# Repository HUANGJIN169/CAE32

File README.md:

# CAE32

CAE32 es un proyecto de construcción y desarrollo de todas las etapas de un volante para videojuegos de PC,
para el sistema operativo de GNU/Linux.

## Las etapas son:

* Diseño PCB
* Firmware
* Driver (Kernel module)
* Configuración y calibración por medio de una interfaz de usuario (GTK-3)
* Diseño de mecanismos para pedales, palanca de cambios y volante
* Diseño PCB de potencia para el control del motor de retroalimentación (FFB)

## Descripción detallada

### Microcontroladores

Para esta primera versión de Harware, se crean 3 PCB

1. Placa principal (ESP32-S3)

2. Placa para la captura de señales analogicas (STM32G070KBT6)

3. Placa con el sensor hall (MT9105ET)

### Firmware

Estoy usando el framework de Espressif (ESP-IDF)

Se usa el microcontrolador STM32G070KBT6, en conjunto con el software
STM32CubeIDE y para programarlo es necesario la utilidad STM32CubeProgrammer,
ademas de una conexión con un "USB-UART bridge"

### Interfaz de usuario

La interfaz está desarrollada con el framework (GTK 3), esta permitirá hacer configuraciones, como por ejemplo:

* Visualización de los datos gráficamente y textual (consola)
* Tipo de transmisión (Manual, Automática, Secuencial, custom) **De forma nativa**
* Límites de los pedales, sensibilidad 
* Tipo de pedal
	* Entrada analógica (Potenciómetro, efecto hall)
	* Entrada SPI,I2c (Célula de carga)
* Actualización de firmware

Diseño de interfaz hasta el momento.

**Para compilar el proyecto puedes usar el contenedor o construirlo en tu sistema(cumpliendo con las dependencias),
revisa la wiki para mas información**

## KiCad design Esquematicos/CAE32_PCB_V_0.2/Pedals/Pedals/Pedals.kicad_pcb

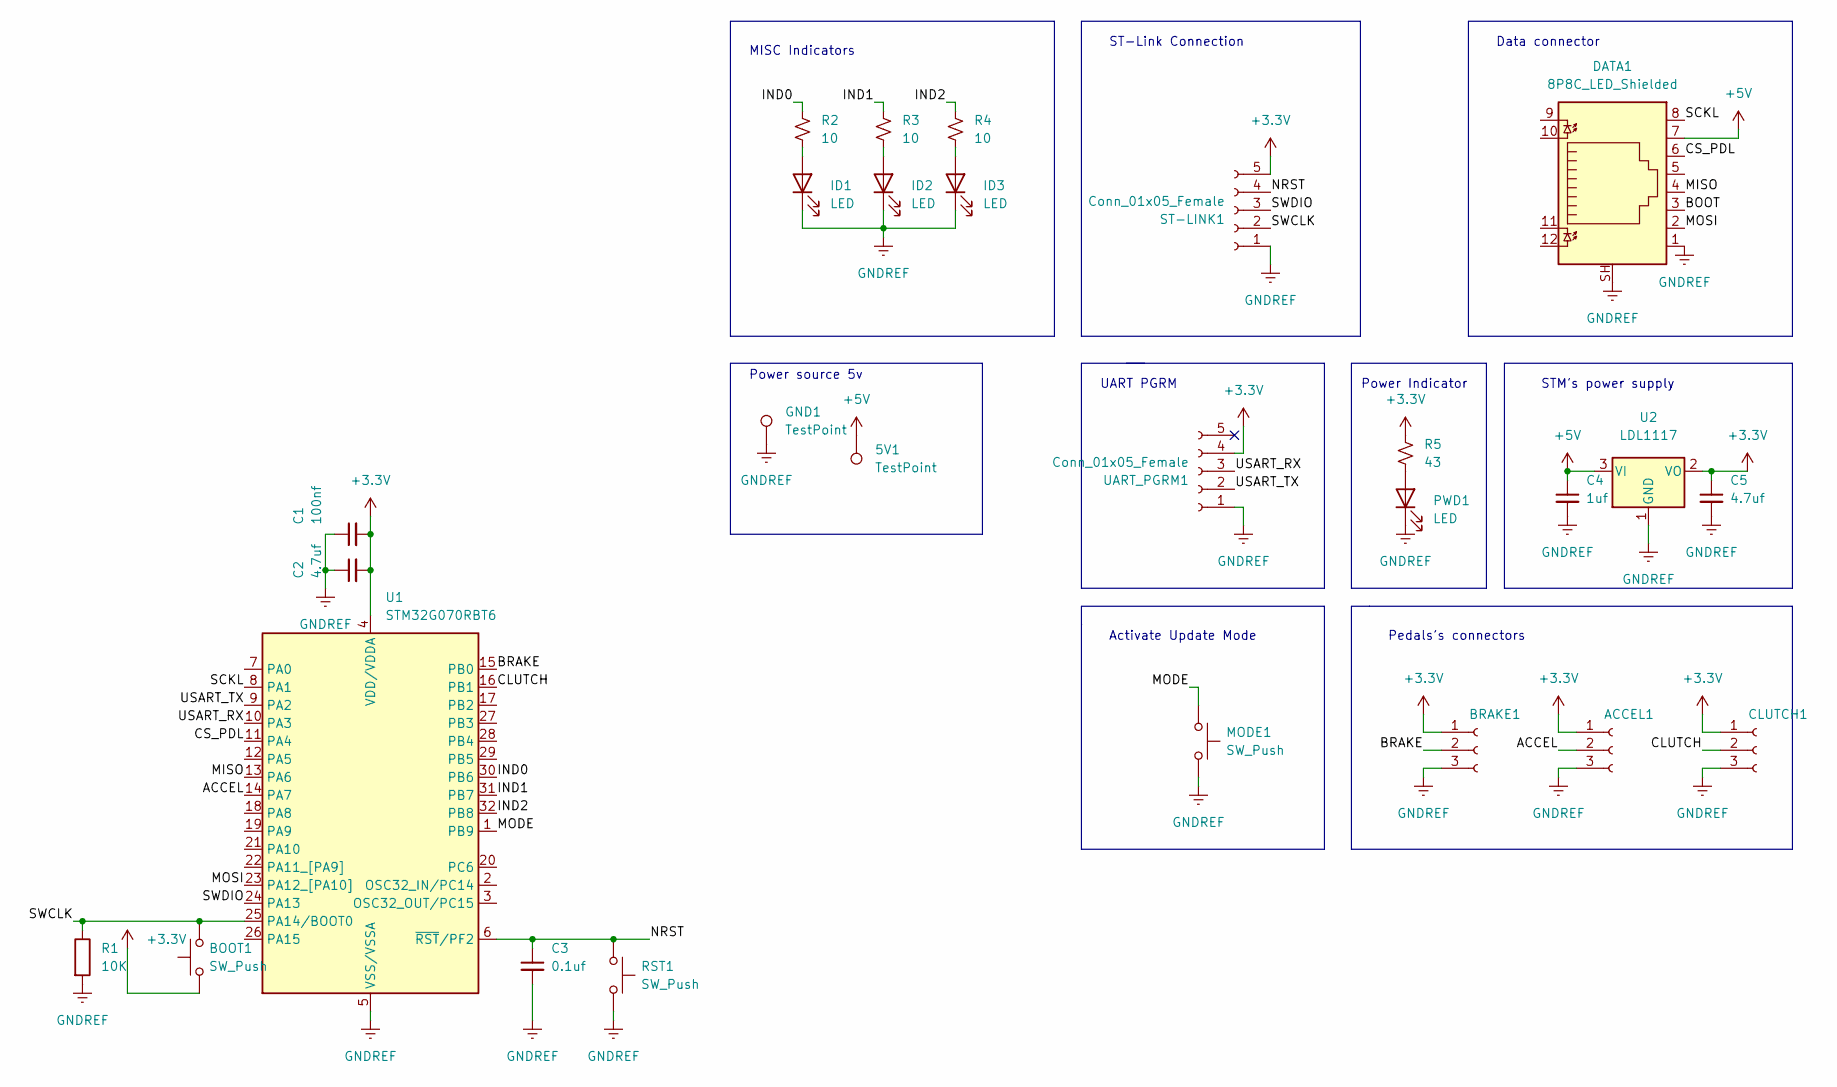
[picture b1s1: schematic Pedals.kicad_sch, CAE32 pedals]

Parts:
5V1: TestPoint; TestPoint_Pad_D3.0mm
ACCEL1: Conn_01x03_Female; JST_EH_B3B-EH-A_1x03_P2.50mm_Vertical
BOOT1: SW_Push; Panasonic_EVQPUM_EVQPUD
BRAKE1: Conn_01x03_Female; JST_EH_B3B-EH-A_1x03_P2.50mm_Vertical
C1: 100nf; C_0805_2012Metric_Pad1.18x1.45mm_HandSolder
C2, C5: 4.7uf; C_0805_2012Metric_Pad1.18x1.45mm_HandSolder
C3: 0.1uf; C_0805_2012Metric_Pad1.18x1.45mm_HandSolder
C4: 1uf; C_0805_2012Metric_Pad1.18x1.45mm_HandSolder
CLUTCH1: Conn_01x03_Female; JST_EH_B3B-EH-A_1x03_P2.50mm_Vertical
DATA1: 8P8C_LED_Shielded; RJ45_Amphenol_RJHSE538X
GND1: TestPoint; TestPoint_Pad_D3.0mm
ID1, ID2, ID3: LED; LED_0805_2012Metric_Pad1.15x1.40mm_HandSolder
MODE1: SW_Push; SW_Push_1P1T_NO_6x6mm_H9.5mm
PWD1: LED; LED_0805_2012Metric_Pad1.15x1.40mm_HandSolder
R1: 10K; R_0805_2012Metric_Pad1.20x1.40mm_HandSolder
R2, R3, R4: 10; R_0805_2012Metric_Pad1.20x1.40mm_HandSolder
R5: 43; R_0805_2012Metric_Pad1.20x1.40mm_HandSolder
RST1: SW_Push; Panasonic_EVQPUM_EVQPUD
ST-LINK1: Conn_01x05_Female; PinHeader_1x05_P2.54mm_Vertical
U1: STM32G070RBT6; LQFP-32_7x7mm_P0.8mm
U2: LDL1117; SOT-223-3_TabPin2
UART_PGRM1: Conn_01x05_Female; PinHeader_1x05_P2.54mm_Vertical

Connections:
+3.3V: ACCEL1.1, BOOT1.1, BRAKE1.1, C1.2, C2.2, C5.1, CLUTCH1.1, R5.1, ST-LINK1.5, U1.4 (VDD/VDDA), U2.2 (VO), UART_PGRM1.4
+5V: 5V1.1, C4.1, DATA1.7, U2.3 (VI)
/ACCEL: ACCEL1.2, U1.14 (PA7)
/BOOT: DATA1.3
/BRAKE: BRAKE1.2, U1.15 (PB0)
/CLUTCH: CLUTCH1.2, U1.16 (PB1)
/CS_PDL: DATA1.6, U1.11 (PA4)
/IND0: R2.1, U1.30 (PB6)
/IND1: R3.1, U1.31 (PB7)
/IND2: R4.1, U1.32 (PB8)
/MISO: DATA1.4, U1.13 (PA6)
/MODE: MODE1.1, U1.1 (PB9)
/MOSI: DATA1.2, U1.23 (PA12_[PA10])
/NRST: C3.1, RST1.1, ST-LINK1.4, U1.6 (~RST/PF2)
/SCKL: DATA1.8, U1.8 (PA1)
/SWCLK: BOOT1.2, R1.1, ST-LINK1.2, U1.25 (PA14/BOOT0)
/SWDIO: ST-LINK1.3, U1.24 (PA13)
/USART_RX: U1.10 (PA3), UART_PGRM1.3
/USART_TX: U1.9 (PA2), UART_PGRM1.2
GNDREF: ACCEL1.3, BRAKE1.3, C1.1, C2.1, C3.2, C4.2, C5.2, CLUTCH1.3, DATA1.1, DATA1.SH, GND1.1, ID1.1 (K), ID2.1 (K), ID3.1 (K), MODE1.2, PWD1.1 (K), R1.2, RST1.2, ST-LINK1.1, U1.5 (VSS/VSSA), U2.1 (GND), UART_PGRM1.1
unnamed: ID1.2 (A), R2.2
unnamed: ID2.2 (A), R3.2
unnamed: ID3.2 (A), R4.2
unnamed: PWD1.2 (A), R5.2

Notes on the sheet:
ST-Link Connection
STM's power supply
Pedals's connectors
Activate Update Mode
Power source 5v
MISC Indicators
Power Indicator
UART PGRM
Data connector

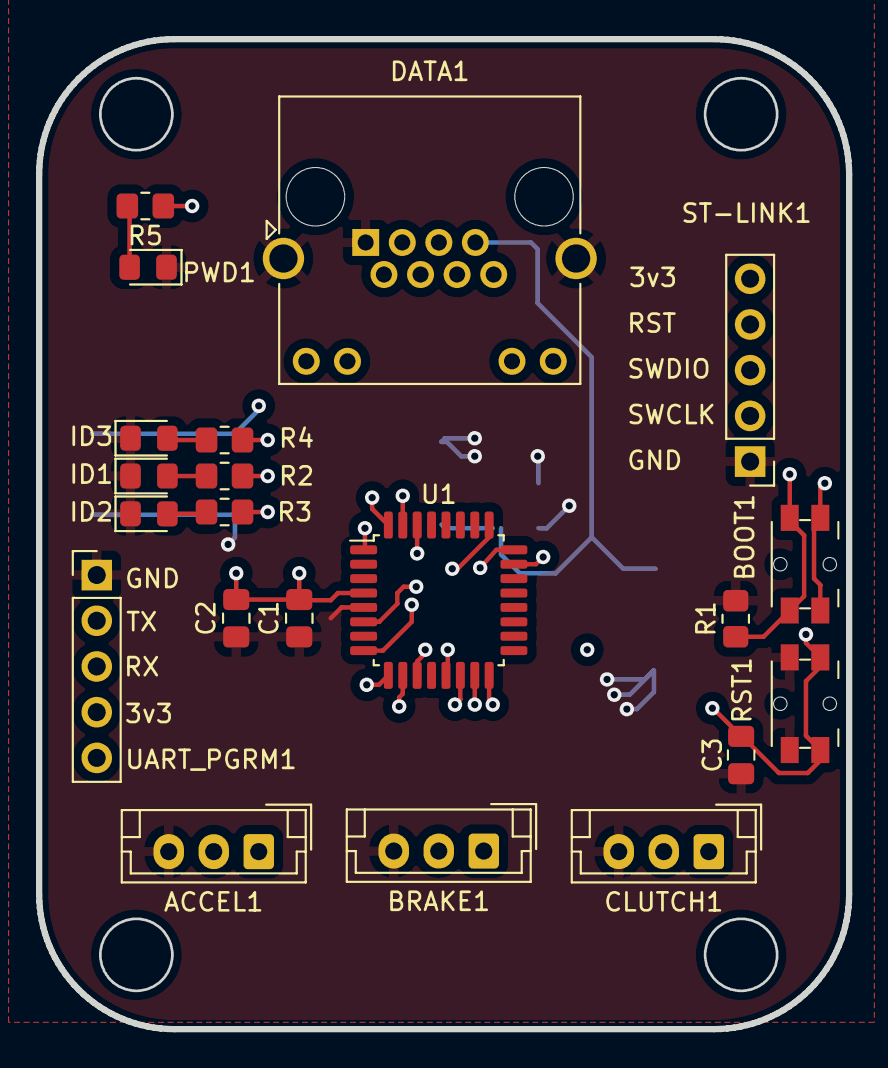
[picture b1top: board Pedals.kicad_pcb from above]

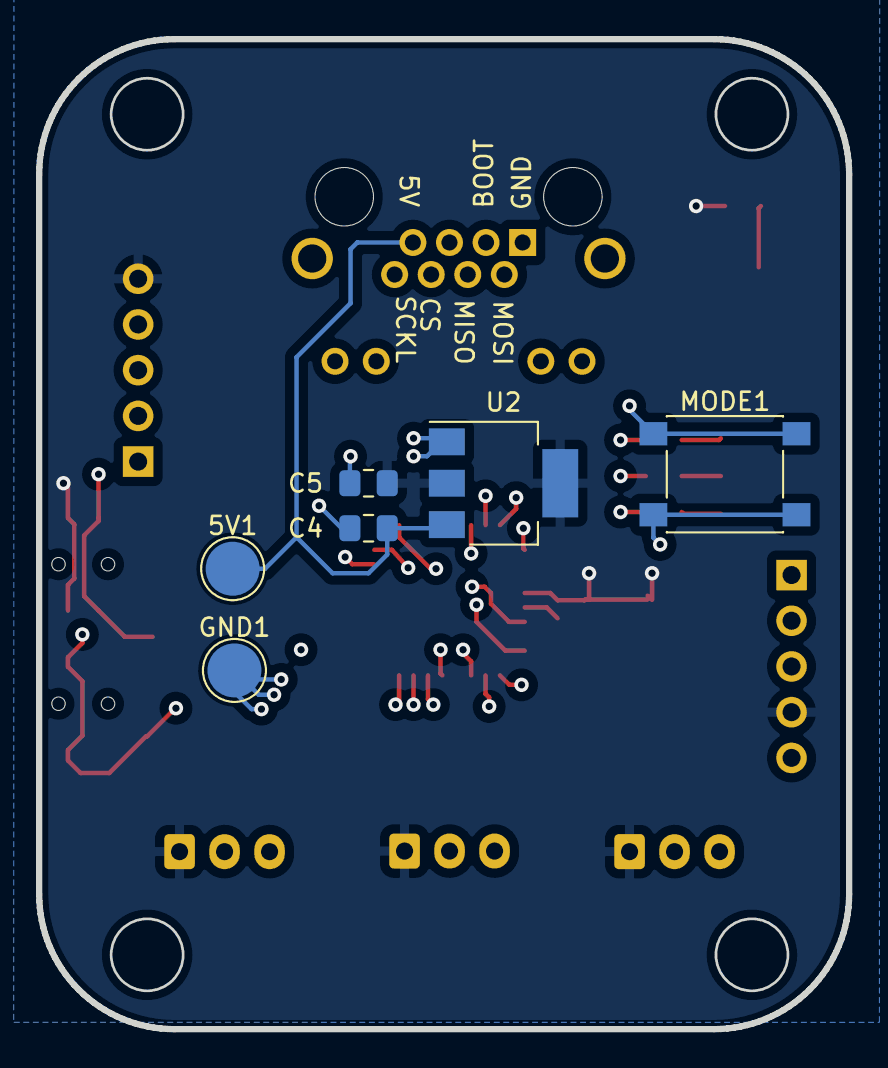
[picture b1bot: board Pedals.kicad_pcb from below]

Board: 4 copper layers, 45.0 x 55.0 mm, 27 parts (6 on the bottom side), 23 nets.

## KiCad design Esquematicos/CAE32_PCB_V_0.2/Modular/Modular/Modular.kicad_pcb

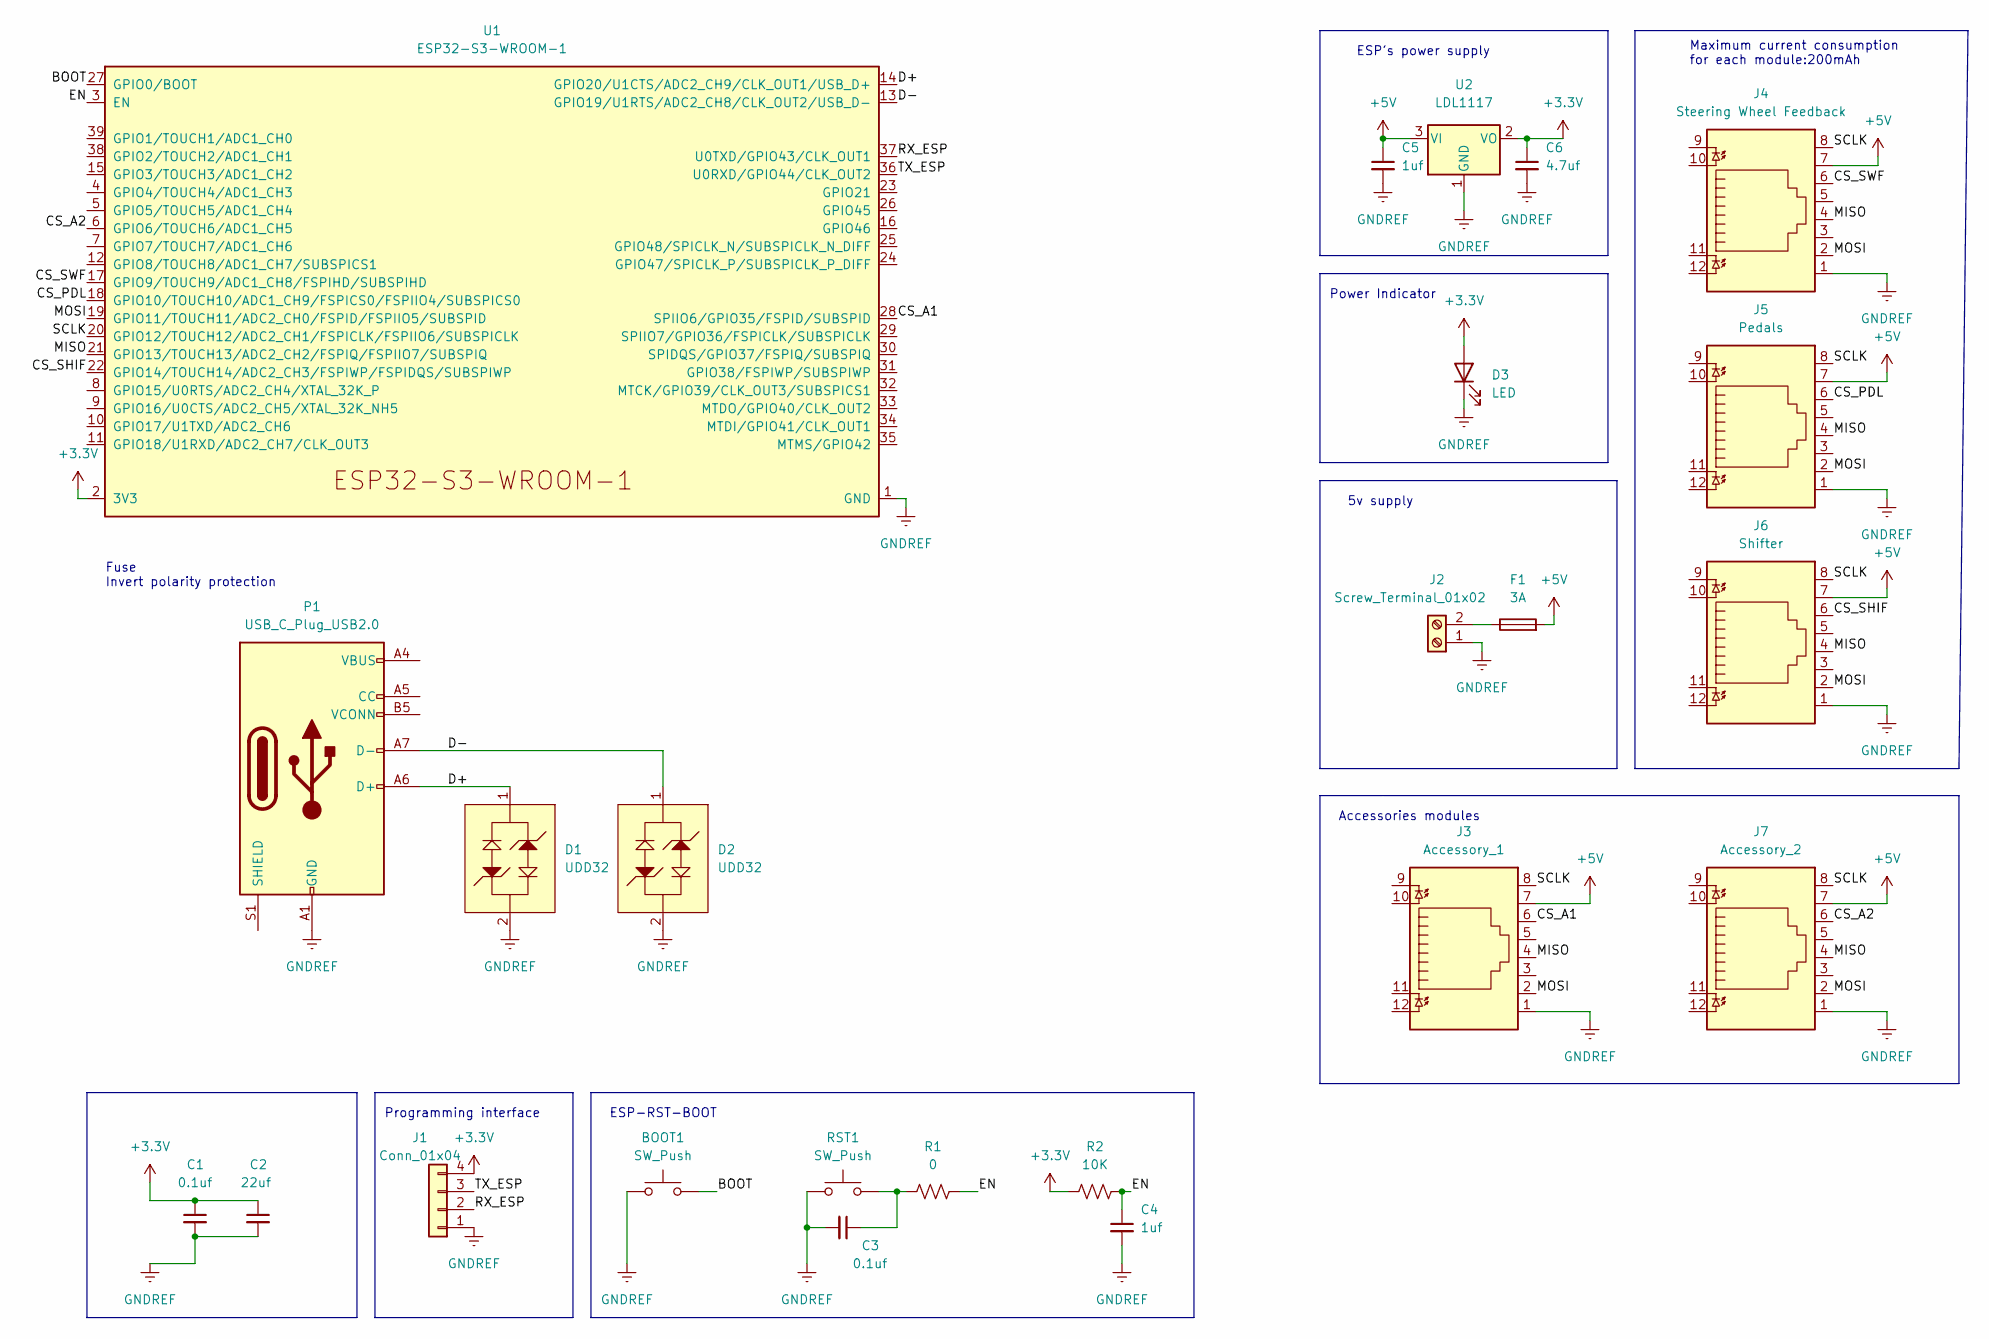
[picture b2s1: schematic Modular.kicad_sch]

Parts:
BOOT1: SW_Push; SW_Push_1P1T_NO_CK_KSC6xxJ
C1, C3: 0.1uf; C_0805_2012Metric_Pad1.18x1.45mm_HandSolder
C2: 22uf; C_0805_2012Metric_Pad1.18x1.45mm_HandSolder
C4, C5: 1uf; C_0805_2012Metric_Pad1.18x1.45mm_HandSolder
C6: 4.7uf; C_0805_2012Metric_Pad1.18x1.45mm_HandSolder
D1, D2: UDD32
D3: LED; LED_0805_2012Metric_Pad1.15x1.40mm_HandSolder
F1: 3A; Fuse_1812_4532Metric_Pad1.30x3.40mm_HandSolder
J1: Conn_01x04; PinHeader_1x04_P2.54mm_Vertical
J2: Screw_Terminal_01x02; TerminalBlock_bornier-2_P5.08mm
J3: Accessory_1; RJ45_Amphenol_RJHSE538X
J4: Steering Wheel Feedback; RJ45_Amphenol_RJHSE538X
J5: Pedals; RJ45_Amphenol_RJHSE538X
J6: Shifter; RJ45_Amphenol_RJHSE538X
J7: Accessory_2; RJ45_Amphenol_RJHSE538X
P1: USB_C_Plug_USB2.0; USB_C_Receptacle_Palconn_UTC16-G
R1: 0; R_0805_2012Metric_Pad1.20x1.40mm_HandSolder
R2: 10K; R_0805_2012Metric_Pad1.20x1.40mm_HandSolder
RST1: SW_Push; SW_Push_1P1T_NO_CK_KSC6xxJ
U1: ESP32-S3-WROOM-1
U2: LDL1117; SOT-223-3_TabPin2

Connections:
+3.3V: C1.1, C2.1, C6.1, D3.2 (A), J1.4, R2.1, U1.2 (3V3), U2.2 (VO)
+5V: C5.1, F1.2, J3.7, J4.7, J5.7, J6.7, J7.7, U2.3 (VI)
/BOOT: BOOT1.2, U1.27 (GPIO0/BOOT)
/CS_A1: J3.6, U1.28 (SPIIO6/GPIO35/FSPID/SUBSPID)
/CS_A2: J7.6, U1.6 (GPIO6/TOUCH6/ADC1_CH5)
/CS_PDL: J5.6, U1.18 (GPIO10/TOUCH10/ADC1_CH9/FSPICS0/FSPIIO4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)
/CS_SHIF: J6.6, U1.22 (GPIO14/TOUCH14/ADC2_CH3/FSPIWP/FSPIDQS/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)
/CS_SWF: J4.6, U1.17 (GPIO9/TOUCH9/ADC1_CH8/FSPIHD/SUBSPIHD)
/D+: D1.1, P1.A6 (D+), U1.14 (GPIO20/U1CTS/ADC2_CH9/CLK_OUT1/USB_D+)
/D-: D2.1, P1.A7 (D-), U1.13 (GPIO19/U1RTS/ADC2_CH8/CLK_OUT2/USB_D-)
/EN: C4.1, R1.2, R2.2, U1.3 (EN)
/MISO: J3.4, J4.4, J5.4, J6.4, J7.4, U1.21 (GPIO13/TOUCH13/ADC2_CH2/FSPIQ/FSPIIO7/S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)
/MOSI: J3.2, J4.2, J5.2, J6.2, J7.2, U1.19 (GPIO11/TOUCH11/ADC2_CH0/FSPID/FSPIIO5/S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)
/RX_ESP: J1.2, U1.37 (U0TXD/GPIO43/CLK_OUT1)
/SCLK: J3.8, J4.8, J5.8, J6.8, J7.8, U1.20 (GPIO12/TOUCH12/ADC2_CH1/FSPICLK/FSPIIO6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)
/TX_ESP: J1.3, U1.36 (U0RXD/GPIO44/CLK_OUT2)
GNDREF: BOOT1.1, C1.2, C2.2, C3.2, C4.2, C5.2, C6.2, D1.2, D2.2, D3.1 (K), J1.1, J2.1, J3.1, J4.1, J5.1, J6.1, J7.1, P1.A1 (GND), P1.A12 (GND), P1.B1 (GND), P1.B12 (GND), RST1.1, U1.1 (GND), U1.40 (GND), U1.41 (GND), U2.1 (GND)
unnamed: C3.1, R1.1, RST1.2
unnamed: F1.1, J2.2
unnamed: P1.A4 (VBUS), P1.A9 (VBUS), P1.B4 (VBUS), P1.B9 (VBUS)

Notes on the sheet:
Fuse Invert polarity protection
Maximum current consumption for each module:200mAh
Power Indicator
Accessories modules
5v supply
Programming interface
ESP's power supply
ESP-RST-BOOT

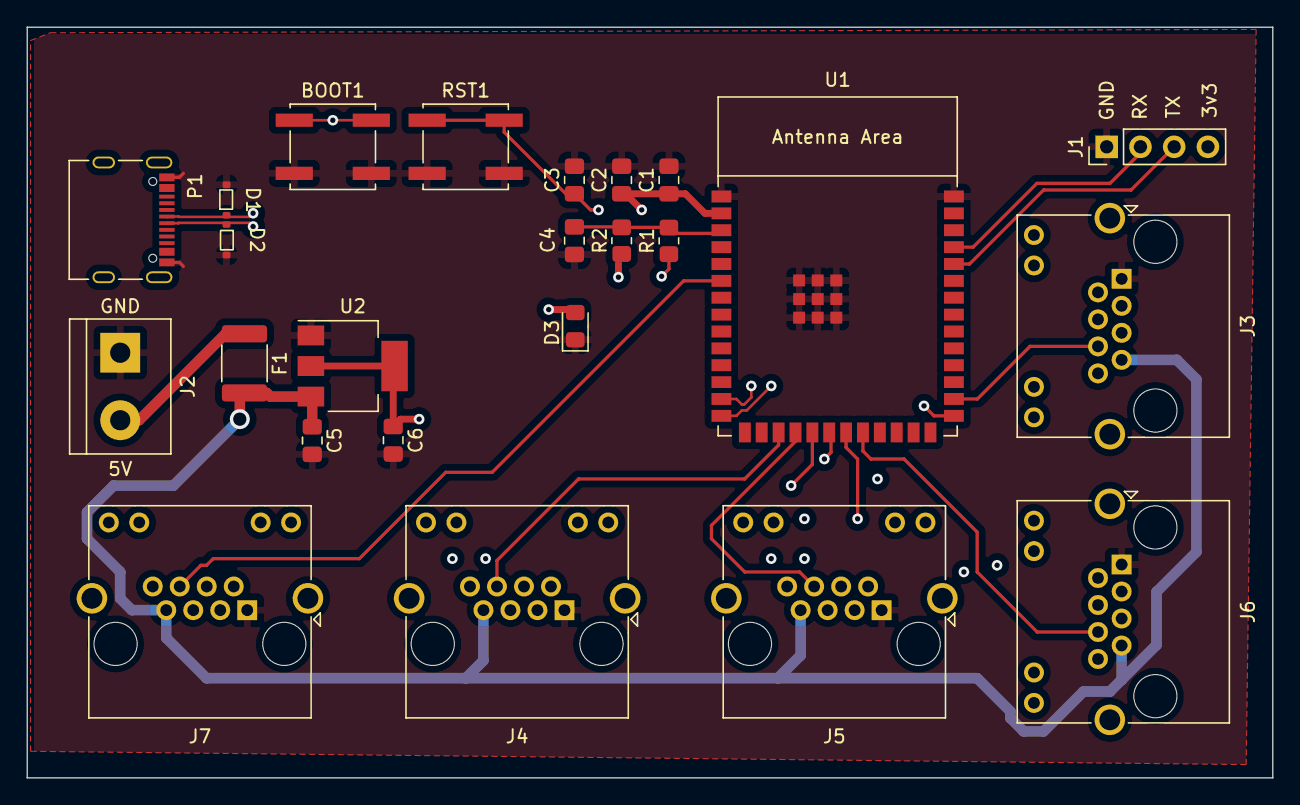
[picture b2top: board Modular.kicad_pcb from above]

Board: 4 copper layers, 93.8 x 56.5 mm, 24 parts (0 on the bottom side), 20 nets.

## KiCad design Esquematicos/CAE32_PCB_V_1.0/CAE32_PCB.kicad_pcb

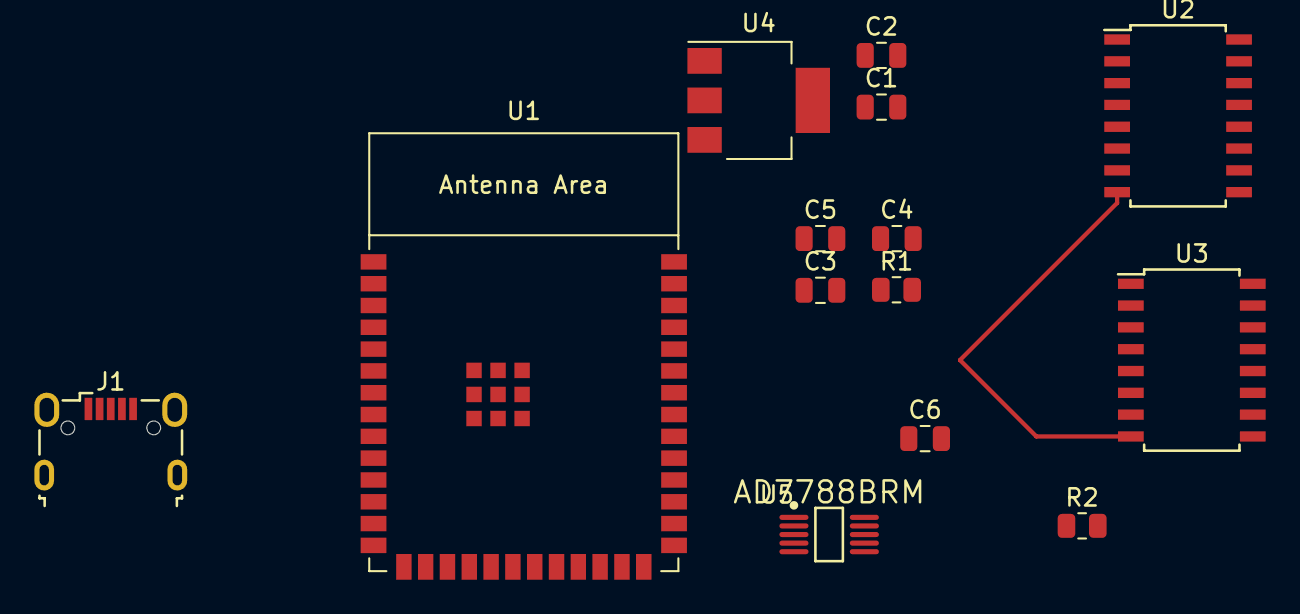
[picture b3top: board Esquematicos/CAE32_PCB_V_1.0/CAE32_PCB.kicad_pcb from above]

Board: 4 copper layers, 14 parts (0 on the bottom side), 5 nets.

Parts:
C1, C2: 10uf; C_0805_2012Metric
C3: 22uf; C_0805_2012Metric
C4, C6: 0.1uf; C_0805_2012Metric
C5: 1uf; C_0805_2012Metric
J1: USB_A; USB_Micro-B_Wuerth_629105150521
R1: 10k; R_0805_2012Metric
R2: 0; R_0805_2012Metric
U1: ESP32-S3-WROOM-1
U2, U3: 74HC4051; SOIC-16W_5.3x10.2mm_P1.27mm
U4: SSP1117; SOT-223-3_TabPin2
U5: AD7788BRM; Analog_Devices-AD7788BRM-Level_B

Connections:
+3.3V: C2.1, C3.1, C4.1, R1.1, U1.2 (3V3), U4.2 (VO)
+5V: C1.1, J1.1 (VBUS), U4.3 (VI)
/EN: C5.2, R1.2, R2.1, U1.3 (EN)
GNDREF: C1.2, C2.2, C3.2, C4.2, C5.1, C6.2, J1.4 (GND), U1.1 (GND), U1.40 (GND), U1.41 (GND), U3.8 (GND), U4.1 (GND)
unnamed: C6.1, R2.2

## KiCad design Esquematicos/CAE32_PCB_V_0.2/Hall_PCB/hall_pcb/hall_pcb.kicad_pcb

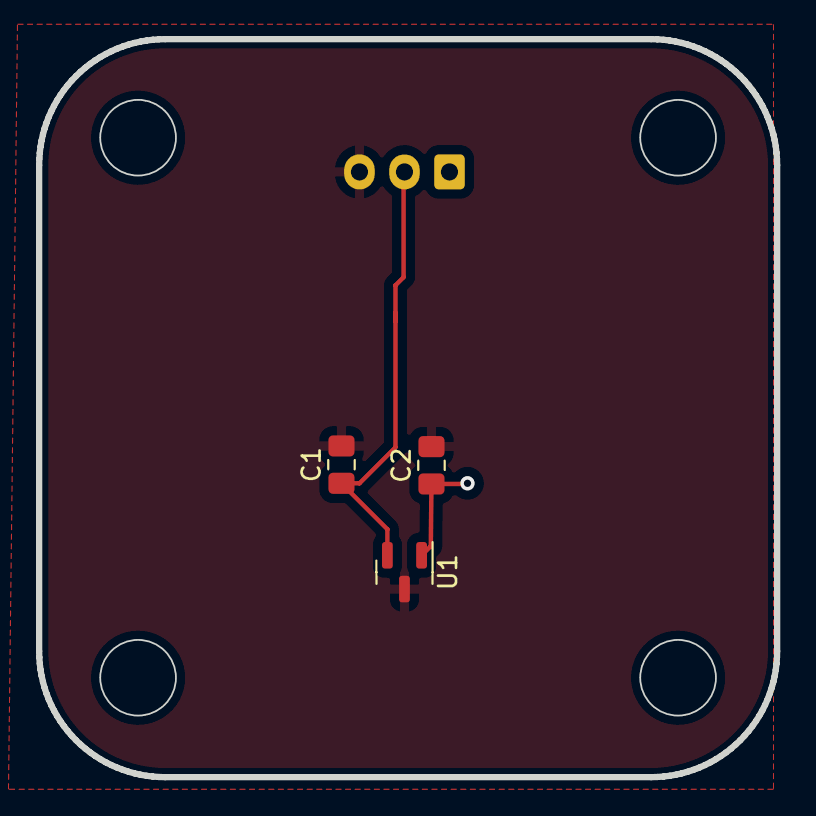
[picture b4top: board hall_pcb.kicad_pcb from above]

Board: 2 copper layers, 41.0 x 41.0 mm, 4 parts (1 on the bottom side), 3 nets.

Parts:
C1: 4.7nf; C_0805_2012Metric_Pad1.18x1.45mm_HandSolder
C2: 100nf; C_0805_2012Metric_Pad1.18x1.45mm_HandSolder
J1: Conn_01x03_Female; JST_EH_B3B-EH-A_1x03_P2.50mm_Vertical
U1: MT9105ET; SOT-23

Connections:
+3V3: C2.1, J1.1, U1.1 (VCC)
/Vout: C1.1, J1.2, U1.2 (OUTPUT)
GNDREF: C1.2, C2.2, J1.3, U1.3 (GND)

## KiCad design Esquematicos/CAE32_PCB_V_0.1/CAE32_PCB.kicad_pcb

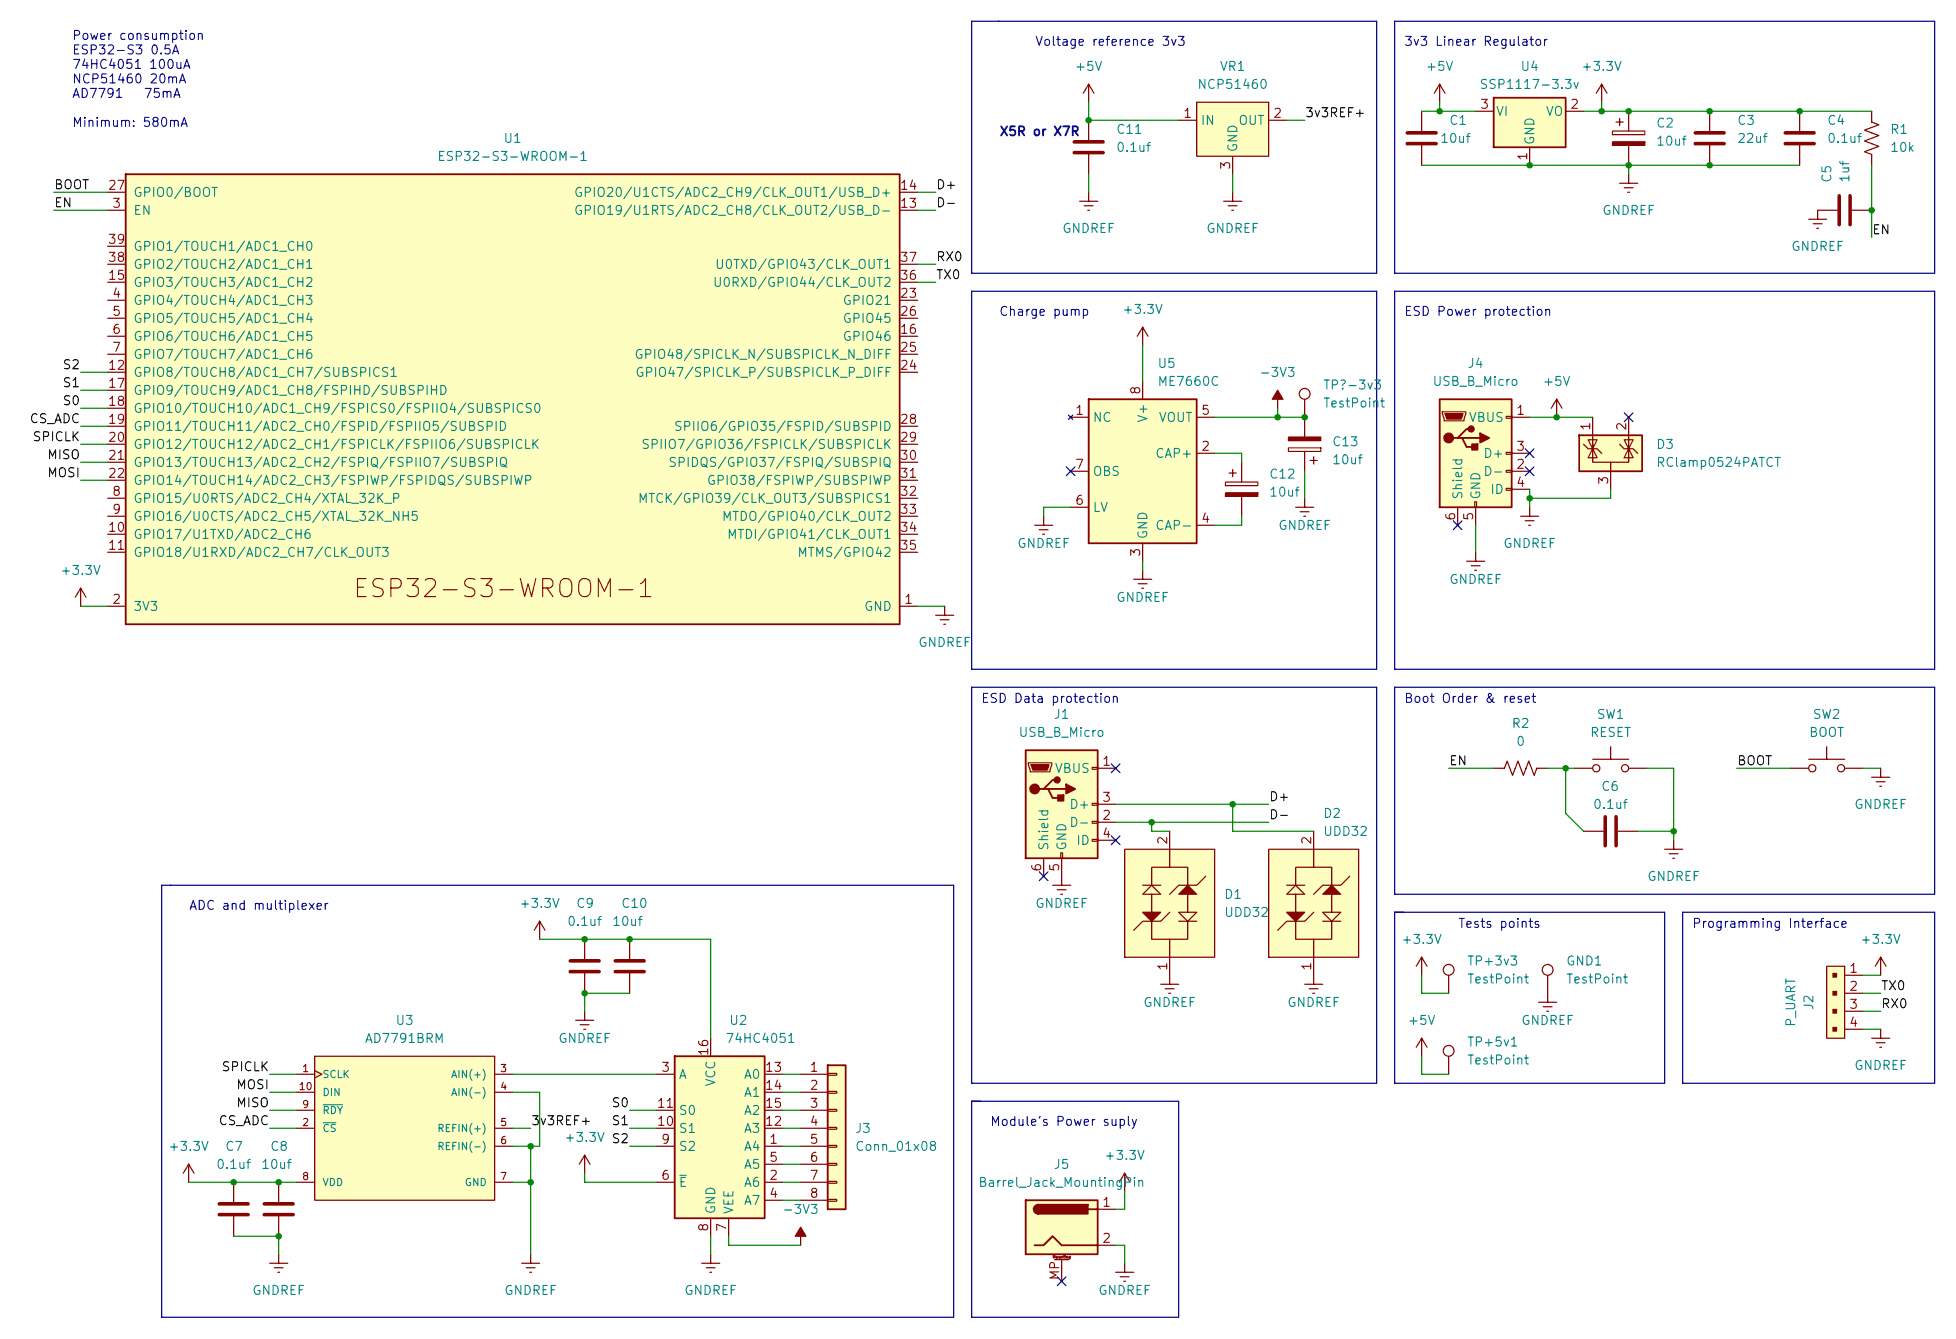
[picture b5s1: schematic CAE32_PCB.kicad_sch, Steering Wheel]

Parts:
C1, C8, C10, C12, C13: 10uf; C_0805_2012Metric
C2: 10uf; D_0805_2012Metric
C3: 22uf; C_0805_2012Metric
C4, C6, C7, C9, C11: 0.1uf; C_0805_2012Metric
C5: 1uf; C_0805_2012Metric
D1, D2: UDD32
D3: RClamp0524PATCT; SOT-23
GND1: TestPoint; TestPoint_Pad_D2.5mm
J1, J4: USB_B_Micro; USB_Micro-B_Amphenol_10118194_Horizontal
J2: P_UART; PinSocket_1x04_P2.54mm_Vertical; MPN 0022232041; Digi-Key_PN WM4202-ND
J3: Conn_01x08; PinSocket_1x08_P2.54mm_Vertical
J5: Barrel_Jack_MountingPin; BarrelJack_Wuerth_6941xx301002
R1: 10k; R_0805_2012Metric
R2: 0; R_0805_2012Metric
SW1: RESET; SW_SPST_PTS810
SW2: BOOT; SW_SPST_PTS810
TP+3v3, TP+5v1: TestPoint; TestPoint_Pad_D2.5mm
TP?-3v3: TestPoint; TestPoint_Pad_D2.5mm
U1: ESP32-S3-WROOM-1
U2: 74HC4051; SOIC-16W_5.3x10.2mm_P1.27mm
U3: AD7791BRM; SSOP-10_3.9x4.9mm_P1.00mm
U4: SSP1117-3.3v; SOT-223-3_TabPin2
U5: ME7660C; SSOP-8_3.9x5.05mm_P1.27mm; LCSC C88402
VR1: NCP51460; SOT-23; MPN REF3030AIDBZR; Digi-Key_PN 296-26323-1-ND

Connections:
+3.3V: C2.1, C3.1, C4.1, C7.1, C8.1, C9.1, C10.1, J2.1, J5.1, R1.1, TP+3v3.1, U1.2 (3V3), U2.6 (~E), U2.16 (VCC), U3.8 (VDD), U4.2 (VO), U5.8 (V+)
+5V: C1.1, C11.1, D3.1 (K), J4.1 (VBUS), TP+5v1.1, U4.3 (VI), VR1.1 (IN)
-3V3: C13.2, TP?-3v3.1, U2.7 (VEE), U5.5 (VOUT)
/3v3REF+: U3.5 (REFIN(+)), VR1.2 (OUT)
/BOOT: SW2.1, U1.27 (GPIO0/BOOT)
/CS_ADC: U1.19 (GPIO11/TOUCH11/ADC2_CH0/FSPID/FSPIIO5/S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), U3.2 (~CS)
/D+: D2.2, J1.3 (D+), U1.14 (GPIO20/U1CTS/ADC2_CH9/CLK_OUT1/USB_D+)
/D-: D1.2, J1.2 (D-), U1.13 (GPIO19/U1RTS/ADC2_CH8/CLK_OUT2/USB_D-)
/EN: C5.2, R1.2, R2.1, U1.3 (EN)
/MISO: U1.21 (GPIO13/TOUCH13/ADC2_CH2/FSPIQ/FSPIIO7/S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), U3.9 (~RDY)
/MOSI: U1.22 (GPIO14/TOUCH14/ADC2_CH3/FSPIWP/FSPIDQS/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), U3.10 (DIN)
/RX0: J2.3, U1.37 (U0TXD/GPIO43/CLK_OUT1)
/S0: U1.18 (GPIO10/TOUCH10/ADC1_CH9/FSPICS0/FSPIIO4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), U2.11 (S0)
/S1: U1.17 (GPIO9/TOUCH9/ADC1_CH8/FSPIHD/SUBSPIHD), U2.10 (S1)
/S2: U1.12 (GPIO8/TOUCH8/ADC1_CH7/SUBSPICS1), U2.9 (S2)
/SPICLK: U1.20 (GPIO12/TOUCH12/ADC2_CH1/FSPICLK/FSPIIO6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), U3.1 (SCLK)
/TX0: J2.2, U1.36 (U0RXD/GPIO44/CLK_OUT2)
GNDREF: C1.2, C2.2, C3.2, C4.2, C5.1, C6.2, C7.2, C8.2, C9.2, C10.2, C11.2, C13.1, D1.1, D2.1, D3.3 (A), GND1.1, J1.5 (GND), J2.4, J4.4 (ID), J4.5 (GND), J5.2, SW1.2, SW2.2, U1.1 (GND), U1.40 (GND), U1.41 (GND), U2.8 (GND), U3.4 (AIN(-)), U3.6 (REFIN(-)), U3.7 (GND), U4.1 (GND), U5.3 (GND), U5.6 (LV), VR1.3 (GND)
unnamed: C6.1, R2.2, SW1.1
unnamed: C12.1, U5.2 (CAP+)
unnamed: C12.2, U5.4 (CAP-)
unnamed: J3.1, U2.13 (A0)
unnamed: J3.2, U2.14 (A1)
unnamed: J3.3, U2.15 (A2)
unnamed: J3.4, U2.12 (A3)
unnamed: J3.5, U2.1 (A4)
unnamed: J3.6, U2.5 (A5)
unnamed: J3.7, U2.2 (A6)
unnamed: J3.8, U2.4 (A7)
unnamed: U2.3 (A), U3.3 (AIN(+))

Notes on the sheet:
Voltage reference 3v3
ADC and multiplexer
ESD Data protection
ESD Power protection
Charge pump
Module's Power suply
Programming Interface
Power consumption ESP32-S3 0.5A 74HC4051 100uA NCP51460 20mA AD7791 75mA Minimum: 580mA
Boot Order & reset
3v3 Linear Regulator
Tests points
X5R or X7R

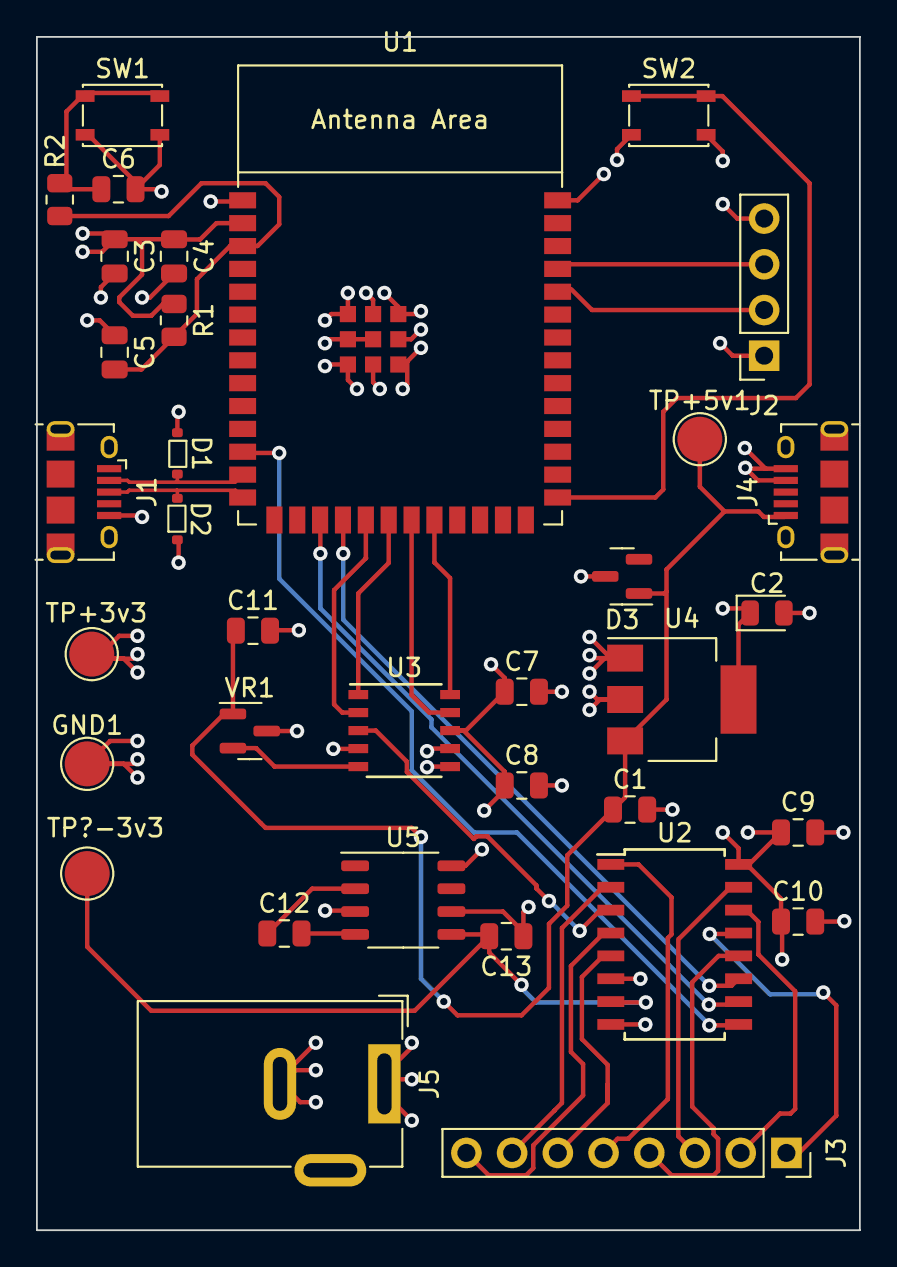
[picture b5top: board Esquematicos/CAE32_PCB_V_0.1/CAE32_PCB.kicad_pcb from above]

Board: 4 copper layers, 45.7 x 66.3 mm, 35 parts (0 on the bottom side), 30 nets.

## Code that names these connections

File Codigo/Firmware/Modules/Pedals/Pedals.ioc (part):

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Mcu.Name=STM32G070KBTx
Mcu.Package=LQFP32
Mcu.UserName=STM32G070KBTx
PA1.Mode=Full_Duplex_Slave
PA1.Signal=SPI1_SCK
PA12\ [PA10].Mode=Full_Duplex_Slave
PA12\ [PA10].Signal=SPI1_MOSI
PA13.Mode=Serial_Wire
PA13.Signal=SYS_SWDIO
PA14-BOOT0.Mode=Serial_Wire
PA14-BOOT0.Signal=SYS_SWCLK
PA4.Mode=NSS_Signal_Hard_Input
PA4.Signal=SPI1_NSS
PA6.Mode=Full_Duplex_Slave
PA6.Signal=SPI1_MISO
PA7.Mode=IN7
PA7.Signal=ADC1_IN7
PB0.Mode=IN8
PB0.Signal=ADC1_IN8
PB1.Mode=IN9
PB1.Signal=ADC1_IN9
PB6.Signal=GPIO_Output
PB7.Signal=GPIO_Output
PB8.Signal=GPIO_Output
PB9.Signal=GPIO_Input
RCC.HSE_VALUE=8000000
RCC.SYSCLKFreq_VALUE=64000000
RCC.SYSCLKSource=RCC_SYSCLKSOURCE_PLLCLK
board=custom

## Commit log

2022-06-15 Create README file
    Se añaden la lista de los primeros componentes
2022-06-15 Correcion de enlaces
2022-06-30 Se subio los archivos del codigo generado en PlatformIO y se agregaron los archivos del banco de pruebas del modulo as5600, tanto de Freecad como en STL
2022-06-30 Se agrego la licencia
2022-07-07 Se crearon los diseños para realizar las pruebas con 4 modulos simultaneamente, además se adjuntan un codigo de prueba usando freertos
2022-09-12 Se cambio el proyecto de Platformio a ESP-IDF
2022-09-14 Se añade documentación
2022-09-14 test agregando terminación md
2022-09-14 Se agrega .md para que encuentre el archivo
2022-09-15 Se agregaron tres modelos para indicador de grados
2022-09-16 Se agrego una configuración automática al encoder y correciones menores a los CAD
2022-09-18 Se agregaron y modificaron archivos freecad además se agrego informacióna a FreeRtos.md
2022-09-18 Creación de una tarea usando FreeRtos
2022-09-19 Cambio de nombre de capeta de codigo y test de construcción
2022-09-19 Cambio de nombre de capeta de codigo y test de construcción 3
2022-09-23 cambios
2022-09-25 Se agregan Urls para lecturas sobre drivers
2022-10-14 Limpieza de área de trabajo
2022-10-14 nuevo esquematico
2022-10-14 nuevos esquematicos
2022-11-02 Creacion de estructuras principales
2022-11-02 Commit para hacer otra branch y organizar mejor el código
2022-11-02 Sanitización de código
2022-11-08 Configuracion y funciones ADC
2022-11-09 Se agrego comunicacion i2c y activacion de encoders
2022-11-10 Se agrego prueba y calibracion de encoders
2022-11-10 Se agrego la lectura de la marcha
2022-11-11 Correciones del algoritmo de valor mapeado encoder y marcha acoplada
2022-11-12 Se añade una funcion para visualizar la trama de datos
2022-11-13 Organizado el nuevo servo e implementacion basica de freertos
2022-11-13 Inicio de esquematicos en kicad
2022-11-14 Se agregaron archivos .md para dar mas informacion
2022-11-17 Visualización de datos en GTK3, no utilizable
2022-11-19 Actualización del archivo README
2022-11-21 Actualización de README con documentación de dispositivo HID
2022-11-21 Actualización de README, Bloques de código
2022-11-22 Se agregaron notas
2022-11-25 Creación de dispostivo virtual
2022-11-29 Identificación del dispositivo en la insterfaz GTK
2022-12-15 Detección de dispositivos (Joystick, HID)
2022-12-25 Primer prototipo de PCB
2022-12-27 Instrucciones para compilar la interfaz y creación de la segunda PCB
2022-12-31 Diseño de Pcb y Boom, de placa de pedales 1.0V
2022-12-31 Actualización de README
2023-01-04 Actualización de Gerbers e indicador de status de conexión
2023-01-10 Uso de GApplication
2023-01-11 Prototipo de función de recolección de entrada
2023-01-12 Implementación de glib
2023-01-17 Funcion para animación de giro
2023-01-21 Visor de cambios terminado y actualización de UI
2023-01-27 Prototipo de actualizaciones y 4 ejes en joystick
2023-01-30 Correciones de errores PCB:pedales y hall
2023-01-31 Ultima revision de PCBs
2023-01-31 Actualización de interfaz en el Readme
2023-01-31 Eliminación de imagene que ya no es necesaria
2023-02-03 Limpieza de directorios
2023-02-04 Se añade un script para crear el acceso directo y mover los archivos al home
2023-03-02 Actualización de README y protipo de actualizador
2023-03-16 reinicio
2023-03-16 add stmcube project
2023-03-16 added esp-idf project for the main board: Spi
2023-03-17 added commands to do the spi communication
2023-03-18 Established SPI's communication between pedals and main board
2023-03-18 Removed Middlewares folder
2023-03-21 Correct communication with SPI
2023-03-27 added files to usb communication, sdkconfig updated and cmake
2023-03-27 Stm32 returns ADC values through SPI correctly
2023-03-27 added notes to future PCB's design
2023-04-17 remove: Imagenes de esquematicos ya no requeridos
2023-04-17 remove: Archivos fp-info-cache de kicad
2023-04-17 Fix: Formato de csv
2023-04-17 Refactor: Renombre de carpea de OAA a uno mas descriptivo
2023-04-17 Refactor: Renombre de carpeta ElementosExtrasPCB a uno mas descriptivo
2023-04-17 Delete: Se elimina archivos de gerber
2023-04-17 Refactor: Renombre de carpeta Boom a BOM y eliminacion de segundo protipo
2023-04-17 Refactor: Renombre de carpeta Boom a BOM
2023-04-17 Refactor: Renombre de carpeta Boom a BOM y eliminacion de archivos csv innecasarios
2023-04-17 Style: Se cambia el formato del csv para que concuerde con los demas
2023-04-17 Delete: Modelos 3d relacionados al componente _UDD32_
2023-04-17 Refactor: Renombre de carpeta de Modelo3D a uno mas descriptivo
2023-04-17 Update: Cambio de nombre del dispositivo a buscar, de Steering Wheel CAE32 a CAE32 Steering Wheel
2023-04-17 add: archivo .clang-format
2023-04-17 Update: Se añade nuevo archivo a compilar al archivo CMakeLists
2023-04-17 Update:Se crean los archivos donde se declaran las tareas que se ejecutaran
2023-04-17 Update: Se crean los archivo para la comunicacion USB y SPI
2023-04-17 Update: Se agrega una nueva regla al gitignore _fp-info-cache_
2023-04-28 Fix: Se corrige el grosor de la pcb a 1.6mm
2023-04-28 Add: se reincorpora el codigo que simula un joystick
2023-04-28 Add: Makefile para construir los dispositivos de simulación
2023-04-28 Add: Archivo para la configuracion de Doxigen
2023-04-28 Update: Se agregan las reglas para :obj executables
2023-04-28 Fix: Se agrega una nueva regla al Makefile para que genere las carpetas en dado caso que no existan
2023-04-28 Delete: Se borran los archivos inncesarios
2023-05-03 Fix: Error al presionar el boton Conectar mas de una vez cuando ya se encontraba conectado el dispositivo
